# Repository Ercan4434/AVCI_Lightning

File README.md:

# AVCI_Lightning
Lightning modules for RC/model aerial vehicles

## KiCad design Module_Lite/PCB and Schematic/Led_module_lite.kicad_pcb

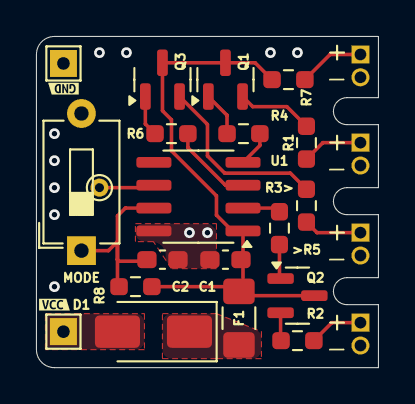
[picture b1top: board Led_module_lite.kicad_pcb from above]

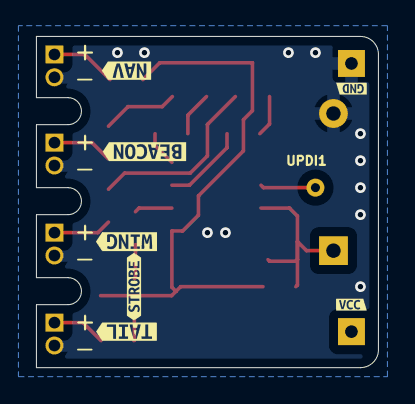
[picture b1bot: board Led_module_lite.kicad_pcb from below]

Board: 2 copper layers, 19.0 x 18.4 mm, 33 parts (7 on the bottom side), 19 nets.

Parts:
>R5: R; R_0603_1608Metric_Pad0.98x0.95mm_HandSolder
C1, C2: 100n; C_0603_1608Metric_Pad1.08x0.95mm_HandSolder
D1: D; D_SMA
F1: Fuse_Small; Fuse_1206_3216Metric_Pad1.42x1.75mm_HandSolder
GND: TestPoint; TestPoint_THTPad_1.5x1.5mm_Drill0.7mm
J1, J2, J3, J4: Conn_01x02; PinHeader_1x02_P1.27mm_Vertical
MODE: SW_SPST; SW_DIP_SPSTx01_Slide_6.7x4.1mm_W7.62mm_P2.54mm_LowProfile
Q1, Q2, Q3: BC817; SOT-23
R1, R2, R3>, R4, R6, R7, R8: R; R_0603_1608Metric_Pad0.98x0.95mm_HandSolder
U1: ATtiny402-SS; SOIC-8_3.9x4.9mm_P1.27mm
UPDI1: UPDI; TestPoint_THTPad_D1.0mm_Drill0.5mm
VCC: TestPoint; TestPoint_THTPad_1.5x1.5mm_Drill0.7mm
kibuzzard-67A246AC: G***; kibuzzard-67A246AC
kibuzzard-67A246B4: G***; kibuzzard-67A246B4
kibuzzard-67A246BB: G***; kibuzzard-67A246BB
kibuzzard-67A248CF: G***; kibuzzard-67A248CF
kibuzzard-67A2469A: G***; kibuzzard-67A2469A
kibuzzard-67A24956, kibuzzard-67A24956#2: G***; kibuzzard-67A24956
kibuzzard-67A24964, kibuzzard-67A24964#2: G***; kibuzzard-67A24964

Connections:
+BATT: D1.2 (A), VCC.1
-BATT: C1.2, C2.2, GND.1, J1.2, J2.2, J3.2, J4.2, MODE.2 (B), U1.8 (GND)
Beacon: J2.1, R1.2
Mode: C2.1, MODE.1 (A), R8.2, U1.7 (PA3)
unnamed: D1.1 (K), F1.1
unnamed: J1.1, R7.2
unnamed: Q1.1 (B), R4.2
unnamed: Q1.2 (E), R1.1
unnamed: >R5.1, Q2.1 (B)
unnamed: Q2.2 (E), R2.1
unnamed: Q3.1 (B), R6.2
unnamed: Q3.2 (E), R3>.1
unnamed: R4.1, U1.4 (PA1)
unnamed: >R5.2, U1.2 (PA6)
unnamed: R6.1, U1.3 (PA7)
unnamed: U1.6 (~RESET/PA0), UPDI1.1
S_tail: J3.1, R2.2
S_wing: J4.1, R3>.2
VCC: C1.1, F1.2, Q1.3 (C), Q2.3 (C), Q3.3 (C), R7.1, R8.1, U1.1 (VCC)

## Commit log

2025-02-06 Create temp
2025-02-06 Rename Module_Lite/PCB an Schematic/temp to Module_Lite/PCB and Schematic
2025-02-06 Rename Led_module_lite.kicad_prl to Led_module_lite.kicad_prl
2025-02-06 Rename Led_module_lite.kicad_pro to Led_module_lite.kicad_pro
2025-02-06 Rename fp-info-cache to fp-info-cache
